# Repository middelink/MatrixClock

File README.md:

# MatrixClock

## TL;DR

MatrixClock is both a hardware and software project to create an extensible
40x8 dot matrix display with some sensors attached because, uhm. I could?

Here you will find the both the schematics, pcb layout and source code of my
MatrixClock project.

## Features

* Based on generaly available red 8x8 dot matrix displays with MAX7219. E.g. on [eBay](https://www.ebay.com/itm/8x8-3mm-5mm-Dot-Matrix-Display-Red-Full-Color-RGB-LED-MAX7219-DIY-Kit-f-Arduino/401374736108) (the red one, with the yellow headers).
* Full source code (arduino, platformio)
* Full schematics, PCB layout and gerbers (kicad)
* ESP-12E/F module for driving display and ntp time keeping.
* USB powered
* User defined button
* Light sensor: APDS9301 and/or BH1750FVI
* Environment sensor: BME280 or BME680
* Extensible, units can be cascaded (only one should have active components though)

## Libraries

* Adafruit's BME680 library has the nasty habbit of initializing the Wire
  library instead of leaving that to the calling program. This means they
  override our carefully set non-standard I2C pins. Needs to be commented
  out around line 104 in Adafruit\_BME680.cpp.
* Same library, Adafruit\_BME680.h, you want to comment out the include of
  Adafruit\_sensor.h. Not there, not used, not needed.

## Installation

The source is written on a Linux box and compiled/uploaded via the excellent
[PlatformIO](https://platformio.org) toolkit. The schematics and pcb layout is
created in [KiCad](https://kicad-pcb.org).

I will not bother to tell you how to compile/upload the code, modify the
schema, change the layout, create gerbers and wait patiently for the PCBs
to arrive before starting your SMD soldering adventure. Simply because
you should not do this if you not exhaustively researched all of the
just mentioned area's.

Good luck!
  Pauline

## License

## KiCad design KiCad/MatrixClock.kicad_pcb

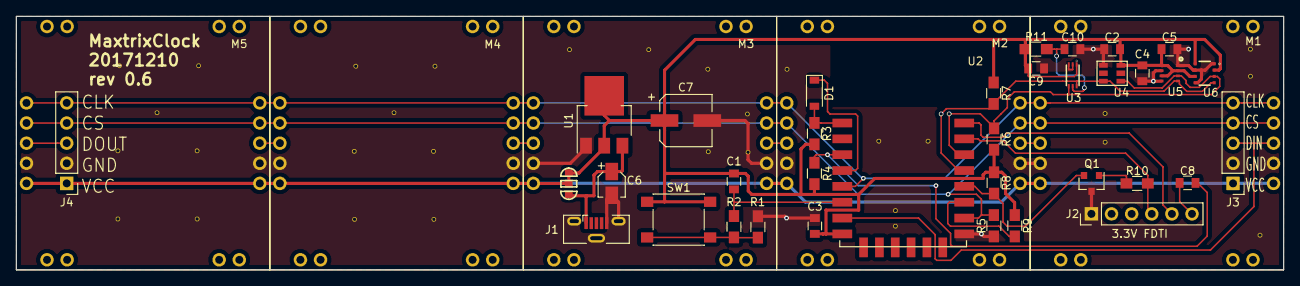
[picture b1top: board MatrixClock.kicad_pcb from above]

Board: 2 copper layers, 160.0 x 32.0 mm, 70 parts (0 on the bottom side), 26 nets.

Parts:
C1, C2, C3, C4, C5, C8, C9, C10: 100nF; C_0805
C6: 10uF; CP_Elec_3x5.3
C7: 100uF; CP_Elec_6.3x5.7
D1: 1N4148; D_SOD-123
J1: USB_OTG; USB_Micro-B_Vertical_Molex-105133-0001
J2: CONN_01X06; Pin_Header_Straight_1x06_Pitch2.54mm
J3, J4: CONN_01X05; Pin_Header_Straight_1x05_Pitch2.54mm
J5: DISP_PWR; SOLDER-JUMPER_2-WAY
M1, M2, M3, M4, M5: Module_MAX7219
Q1: PNP; SOT-23
R1, R2: 100K; R_0805_HandSoldering
R3, R4, R5, R6, R7, R8, R9: 10K; R_0805_HandSoldering
R10: 4K7; R_0805_HandSoldering
R11: 1K; R_0805_HandSoldering
SW1: SW_Push; SW_SPST_PTS645
U1: LD1117S33TR; SOT-223-3Lead_TabPin2
U2: ESP-12E; ESP-12E_SMD
U3: BH1750FVI-TR; WSOF6
U4: APDS-9301; APDS9301
U5: BME280
U6: BME680
VIA01, VIA02, VIA03, VIA04, VIA05, VIA06, VIA07, VIA07#2, VIA08, VIA09, VIA10, VIA11, VIA12, VIA13, VIA14, VIA15, VIA17, VIA20, VIA21, VIA22, VIA23, VIA23#2, VIA23#3, VIA24, VIA26, VIA26#2, VIA27, VIA28, VIA29, VIA31: VIA-6mm

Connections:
+3V3: C1.1, C2.2, C3.1, C4.2, C5.2, C7.1, C9.2, J5.3, R3.1, R4.1, R6.1, R7.1, R8.1, R9.1, R11.1, SW1.1, U1.2, U2.8, U3.1, U4.1, U5.2, U5.6, U5.8, U6.2, U6.6, U6.8
/CH_PD: C8.2, R4.2, U2.3
/CLK: J3.5, J4.5, M1.1, M2.1, M3.1, M4.1, M5.1, U2.5
/CS: J3.4, J4.4, M1.2, M2.2, M3.2, M4.2, M5.2, R5.1, U2.10
/DTR: C8.1, J2.6
/D_PWR: J3.1, J4.1, J5.2, M1.5, M2.5, M3.5, M4.5, M5.5
/GPIO0: Q1.2, R8.2, U2.12
/MOSI: J3.3, M1.3, U2.7
/MOSI_OUT: J4.3, M5.6
/RxD: J2.4, R10.1, U2.15
/SCL: R7.2, U2.13, U3.6, U4.4, U5.4, U6.4
/SDA: R6.2, U2.14, U3.4, U4.5, U5.3, U6.3
/TxD: J2.5, U2.16
GND: C2.1, C3.2, C4.1, C5.1, C6.2, C7.2, C9.1, C10.1, J1.5, J1.6, J2.1, J3.2, J4.2, M1.4, M2.4, M3.4, M4.4, M5.4, Q1.3, R1.1, R5.2, U1.1, U2.9, U3.2, U3.3, U4.2, U5.1, U5.5, U5.7, U6.1, U6.5, U6.7, VIA01.1, VIA02.1, VIA03.1, VIA04.1, VIA05.1, VIA06.1, VIA07.1, VIA07#2.1, VIA08.1, VIA09.1, VIA10.1, VIA11.1, VIA12.1, VIA13.1, VIA14.1, VIA15.1, VIA17.1, VIA20.1, VIA21.1, VIA22.1, VIA23.1, VIA23#2.1, VIA23#3.1, VIA24.1, VIA26.1, VIA26#2.1, VIA27.1, VIA28.1, VIA29.1, VIA31.1
unnamed: C1.2, R2.1, U2.6
unnamed: C10.2, R11.2, U3.5
unnamed: D1.1, U2.4
unnamed: D1.2, R3.2, U2.1
unnamed: M1.6, M2.3
unnamed: M2.6, M3.3
unnamed: M3.6, M4.3
unnamed: M4.6, M5.3
unnamed: Q1.1, R10.2
unnamed: R1.2, R2.2, SW1.2
unnamed: R9.2, U2.11
VCC: C6.1, J1.1, J5.1, U1.3

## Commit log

2017-11-22 Initial commit of rev 0.3
2017-11-22 Bumped version to 0.5
    Features:
    * Reworked the matrix module layout, the 2 header pins where 0.4mm off.
    * Added BH1750FVI as an alternative light sensor.
    Fixed issues:
    * R10 should be connected to RX, not TX (seen from ESP12, not FTDI connector)
2017-11-23 Same revision, regenerated GERBER files and re-added .png and .zip for easy submitting to your fav pcbfab studio.
2017-11-25 Set (long) timeout on Wifimanager, to handle rebooting APs and have all your clocks/sensors jump into AP mode.
    Updated .gitignore to ignore platformio's build directories.
2017-11-25 BME280 library got updated in an non-backward compatible manner.
2017-11-25 "Upgrade" lib/apds9301 from a submodule to an included library. (Otherwise my changes won't be visible; https://github.com/jlz3008/apds9301/pull/1)
2017-12-08 New version of platformio removed espress8266_stage support. Instead they want us to use a github url.
2017-12-08 apds9301 library cleanup. Mostly comments and tab > 4 spaces.
2017-12-08 Remove unneeded mqtt_subscribe Add BH1750FVI light sensor option in rev 0.5
2017-12-18 New release 0.6, discovered a stray stitch via in the middle of the regulator solder pad. Moved other stitch via's around for a more visual appealing pattern ^^
2017-12-18 Library changes to apds9301 were accepted by github author, and were also as PlatformIO library. Removing my fork as it has become unnecessary.
2019-03-02 Update build files to new world. Fixed some small issues with wifimanager timeouts.
2021-01-03 Add license scan report and status
    Signed off by: fossabot <badges@fossa.com>
